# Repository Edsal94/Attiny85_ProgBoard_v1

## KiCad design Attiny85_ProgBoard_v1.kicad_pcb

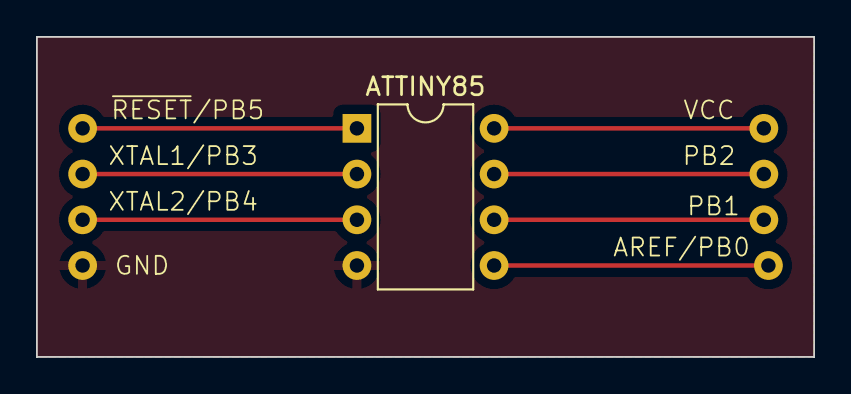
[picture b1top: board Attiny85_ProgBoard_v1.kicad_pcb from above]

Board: 2 copper layers, 43.2 x 17.8 mm, 8 parts (0 on the bottom side), 7 nets.

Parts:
AREF/PB0: Conn_01x01_Female; PinHole_01x01
ATTINY85: ATtiny85V-10PU; DIP-8_W7.62mm
GND: Conn_01x01_Female; PinHole_01x01
PB1, PB2: Conn_01x01_Female; PinHole_01x01
VCC: Conn_01x01_Female; PinHole_01x01
XTAL1/PB3, XTAL2/PB4: Conn_01x01_Female; PinHole_01x01

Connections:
unnamed: AREF/PB0.1, ATTINY85.5 (AREF/PB0)
unnamed: ATTINY85.4 (GND), GND.1
unnamed: ATTINY85.6 (PB1), PB1.1
unnamed: ATTINY85.7 (PB2), PB2.1
unnamed: ATTINY85.8 (VCC), VCC.1
unnamed: ATTINY85.2 (XTAL1/PB3), XTAL1/PB3.1
unnamed: ATTINY85.3 (XTAL2/PB4), XTAL2/PB4.1

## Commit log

2022-10-09 First commit_fixed
2022-10-11 Added Attiny85 schematic symbol and footprint
2022-11-05 added datasheet
2023-04-10 worked on PCB design
2023-04-12 Designed PCB
2023-04-12 Created folder for Gerber files
2023-05-21 Added GND planes on top layer
2023-05-24 Added dedicated library
